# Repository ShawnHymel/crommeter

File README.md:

# Crommeter SAO

> SHOW ME WHAT YOU GOT

Badge accessory (SAO) to measure general sound level from cheers and applause. Gives a (somewhat) precise measurement of sound pressure level in dB.

This was made in Rust for no other reason than to test my embedded Rust skills.

## Build the Project

To build the project, you'll need Rust on your computer. Follow the [instructions here to install Rust](https://www.rust-lang.org/tools/install).

Next, install the Thumbv8m target processor:

```sh
rustup target add thumbv8m.main-none-eabihf
```

Navigate into the firmware directory and build the project:

```sh
cd firmware/crommeter/
cargo build --release
```

You can either flash the output ELF file (in *target/thumbv8m.main-none-eabihf/release*) using the [Raspberry Pi Debug Probe](https://www.raspberrypi.com/documentation/microcontrollers/debug-probe.html) or you can convert the ELF file to a UF2 file to flash over the USB mass storage device bootloader. To do the latter, you'll need to install [picotool](https://github.com/raspberrypi/picotool).

## (Optional) Install picotool

I recommend downloading one of the pre-compiled releases of picotool from [here](https://github.com/raspberrypi/pico-sdk-tools/releases). Unzip the file somewhere on your computer.

### Windows

Copy the *picotool/* folder to a place like *C:\Program Files\picotool\*.

Update PATH:

 1. Press **Win + R**, type `sysdm.cpl`, press **Enter**
 2. Go to the **Advanced** tab and click **Environment Variables**
 3. Under *User variables* or *System variables*, find *Path*
 4. Click **Edit > New** and add: `C:\Program Files\picotool`
 5. Click **OK** on all dialogs
 6. Restart your terminal/command prompt

### Linux

Copy picotool to your user local bin folder:

```sh
mkdir -p ~/.local/bin
cp picotool ~/.local/bin/
chmod +x ~/.local/bin/picotool
```

Update PATH: add the following to *~/.bashrc*:

```sh
export PATH="$HOME/.local/bin:$PATH"
```

Reload:

```sh
source ~/.bashrc
```

### macOS

Copy picotool to your user local bin folder:

```sh
mkdir -p ~/.local/bin
cp picotool ~/.local/bin/
chmod +x ~/.local/bin/picotool
```

Update PATH: add the following to *~/.zshrc*:

```sh
export PATH="$HOME/.local/bin:$PATH"
```

Reload:

```sh
source ~/.zshrc
```

## Run picotool and Flash

Once you have picotool installed, you can convert the ELF file to a UF2 file. Navigate to the firmware's directory and run:

```sh
cd firmware/crommeter/
picotool uf2 convert target/thumbv8m.main-none-eabihf/release/crommeter -t elf firmware.uf2
```

Hold the BOOT button on the RP2350 stamp and press/release the RESET button while the board is plugged into your computer. That should put the RP2350 into bootloader mode, which enumerates as a mass storage device on your computer. Then, simply copy the *firmware.uf2* file you just created to the RP2350 drive. The board should automatically reset and start running the firmware!

## License

The hardware files are released under [Creative Commons Attribution 4.0 International (CC BY 4.0)](https://creativecommons.org/licenses/by/4.0/).

Code in the firmware directory, unless otherwise noted, is licensed under the [Zero-Clause BSD license](https://opensource.org/license/0bsd) (0BSD).

```
Zero-Clause BSD
=============

Permission to use, copy, modify, and/or distribute this software for
any purpose with or without fee is hereby granted.

THE SOFTWARE IS PROVIDED “AS IS” AND THE AUTHOR DISCLAIMS ALL
WARRANTIES WITH REGARD TO THIS SOFTWARE INCLUDING ALL IMPLIED WARRANTIES
OF MERCHANTABILITY AND FITNESS. IN NO EVENT SHALL THE AUTHOR BE LIABLE
FOR ANY SPECIAL, DIRECT, INDIRECT, OR CONSEQUENTIAL DAMAGES OR ANY
DAMAGES WHATSOEVER RESULTING FROM LOSS OF USE, DATA OR PROFITS, WHETHER IN
AN ACTION OF CONTRACT, NEGLIGENCE OR OTHER TORTIOUS ACTION, ARISING OUT
OF OR IN CONNECTION WITH THE USE OR PERFORMANCE OF THIS SOFTWARE.
```

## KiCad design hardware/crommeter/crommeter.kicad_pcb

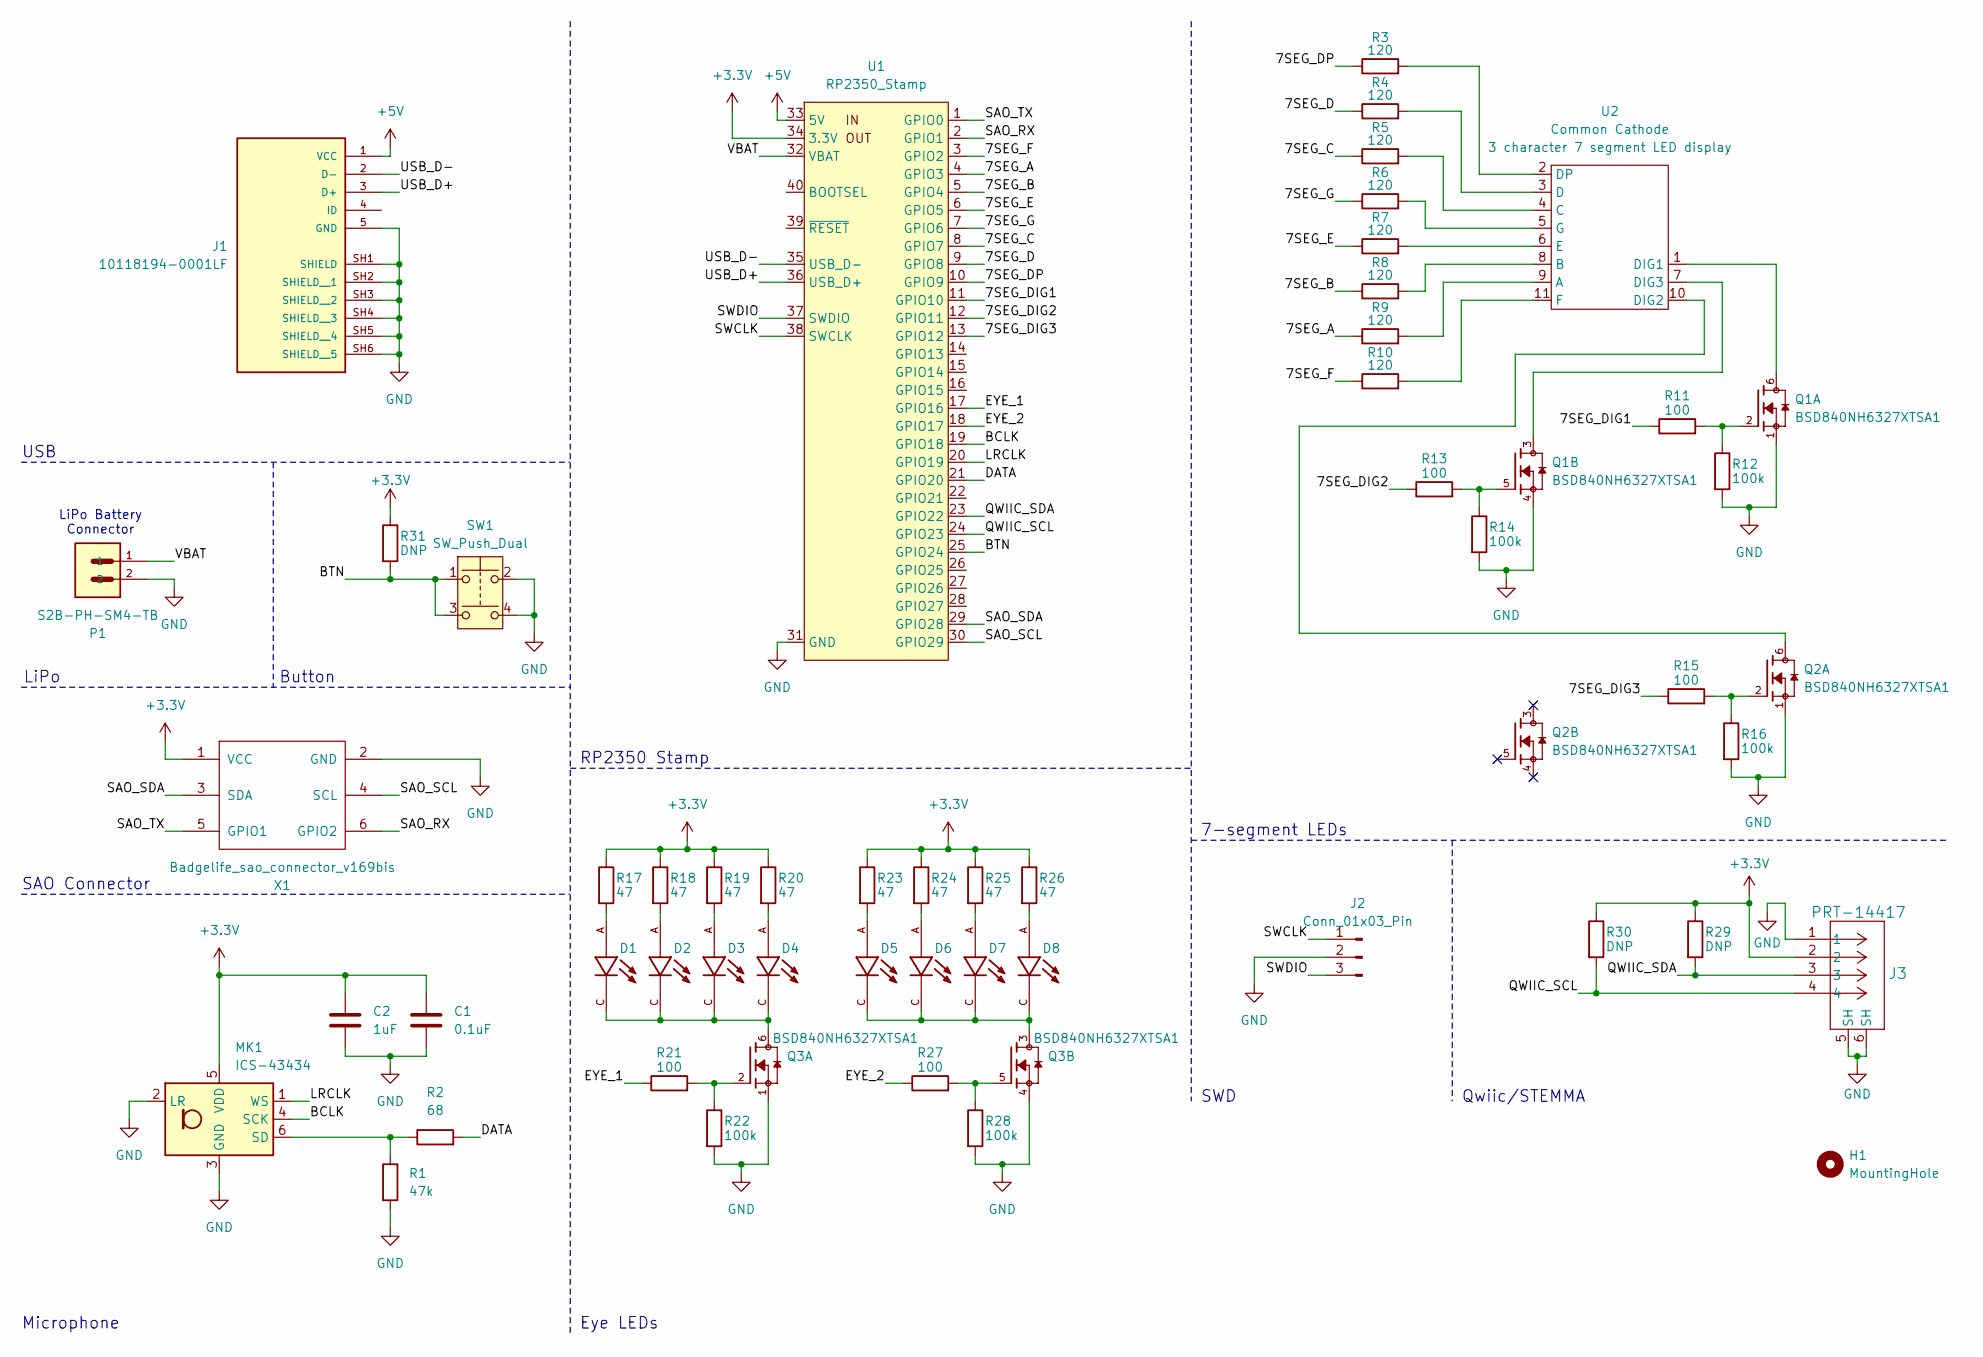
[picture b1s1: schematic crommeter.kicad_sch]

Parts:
C1: 0.1uF; C_0603_1608Metric_Pad1.08x0.95mm_HandSolder
C2: 1uF; C_0603_1608Metric_Pad1.08x0.95mm_HandSolder
D1, D2, D3, D4, D5, D6, D7, D8: CUW_Y3SH.B2-GFJD-5J6T-Z242-20-R18-Z; LED_CUW_Y3SH.B2-GFJD-5J6T-Z242-20-R18-Z; PARTREV 1.0
H1: MountingHole; MountingHole_4.3mm_M4
J1: 10118194-0001LF; AMPHENOL_10118194-0001LF; PARTREV D
J2: Conn_01x03_Pin; AMPHENOL_10129380-903001BLF
J3: PRT-14417; CONN_PRT-14417_SPK
MK1: ICS-43434; InvenSense_ICS-43434-6_3.5x2.65mm
P1: S2B-PH-SM4-TB; JST_S2B-PH-SM4-TB
Q1, Q2, Q3: BSD840NH6327XTSA1; TRANS_BSD840NH6327XTSA1; PARTREV 2.4
R1: 47k; R_0603_1608Metric_Pad0.98x0.95mm_HandSolder
R2: 68; R_0603_1608Metric_Pad0.98x0.95mm_HandSolder
R3, R4, R5, R6, R7, R8, R9, R10: 120; R_0603_1608Metric_Pad0.98x0.95mm_HandSolder
R11, R13, R15, R21, R27: 100; R_0603_1608Metric_Pad0.98x0.95mm_HandSolder
R12, R14, R16, R22, R28: 100k; R_0603_1608Metric_Pad0.98x0.95mm_HandSolder
R17, R18, R19, R20, R23, R24, R25, R26: 47; R_0603_1608Metric_Pad0.98x0.95mm_HandSolder
R29, R30, R31: DNP; R_0603_1608Metric_Pad0.98x0.95mm_HandSolder
SW1: SW_Push_Dual; SWITCH_FSM2JSMAA_TYC
U1: RP2350_Stamp; RP2xxx_Stamp_SMD
U2: Common Cathode; SDTx40R2W
X1: Badgelife_sao_connector_v169bis; Badgelife-SAOv169-SAO-2x3

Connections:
+3.3V: C1.1, C2.1, J3.2, MK1.5 (VDD), R17.1, R18.1, R19.1, R20.1, R23.1, R24.1, R25.1, R26.1, R29.1, R30.1, R31.1, U1.34 (3.3V), X1.1 (VCC)
+5V: J1.1 (VCC), U1.33 (5V)
/7SEG_A: R9.1, U1.4 (GPIO3)
/7SEG_B: R8.1, U1.5 (GPIO4)
/7SEG_C: R5.1, U1.8 (GPIO7)
/7SEG_D: R4.1, U1.9 (GPIO8)
/7SEG_DIG1: R11.1, U1.11 (GPIO10)
/7SEG_DIG2: R13.1, U1.12 (GPIO11)
/7SEG_DIG3: R15.1, U1.13 (GPIO12)
/7SEG_DP: R3.1, U1.10 (GPIO9)
/7SEG_E: R7.1, U1.6 (GPIO5)
/7SEG_F: R10.1, U1.3 (GPIO2)
/7SEG_G: R6.1, U1.7 (GPIO6)
/<NO NET>: U1.29 (GPIO28), X1.3 (SDA)
/BCLK: MK1.4 (SCK), U1.19 (GPIO18)
/BTN: R31.2, SW1.1, SW1.3, U1.25 (GPIO24)
/DATA: R2.2, U1.21 (GPIO20)
/EYE_1: R21.1, U1.17 (GPIO16)
/EYE_2: R27.1, U1.18 (GPIO17)
/LRCLK: MK1.1 (WS), U1.20 (GPIO19)
/QWIIC_SCL: J3.4, R30.2, U1.24 (GPIO23)
/QWIIC_SDA: J3.3, R29.2, U1.23 (GPIO22)
/SAO_RX: U1.2 (GPIO1), X1.6 (GPIO2)
/SAO_SCL: U1.30 (GPIO29), X1.4 (SCL)
/SAO_TX: U1.1 (GPIO0), X1.5 (GPIO1)
/SWCLK: J2.1, U1.38 (SWCLK)
/SWDIO: J2.3, U1.37 (SWDIO)
/USB_D+: J1.3 (D+), U1.36 (USB_D+)
/USB_D-: J1.2 (D-), U1.35 (USB_D-)
/VBAT: P1.1, U1.32 (VBAT)
GND: C1.2, C2.2, J1.5 (GND), J1.SH1 (SHIELD), J1.SH2 (SHIELD__1), J1.SH3 (SHIELD__2), J1.SH4 (SHIELD__3), J1.SH5 (SHIELD__4), J1.SH6 (SHIELD__5), J2.2, J3.1, J3.5 (SH), J3.6 (SH), MK1.2 (LR), MK1.3 (GND), P1.2, Q1.1, Q1.4, Q2.1, Q3.1, Q3.4, R1.2, R12.2, R14.2, R16.2, R22.2, R28.2, SW1.2, SW1.4, U1.31 (GND), X1.2 (GND)
unnamed: D1.A, R17.2
unnamed: D1.C, D2.C, D3.C, D4.C, Q3.6
unnamed: D2.A, R18.2
unnamed: D3.A, R19.2
unnamed: D4.A, R20.2
unnamed: D5.A, R23.2
unnamed: D5.C, D6.C, D7.C, D8.C, Q3.3
unnamed: D6.A, R24.2
unnamed: D7.A, R25.2
unnamed: D8.A, R26.2
unnamed: MK1.6 (SD), R1.1, R2.1
unnamed: Q1.2, R11.2, R12.1
unnamed: Q1.5, R13.2, R14.1
unnamed: Q2.2, R15.2, R16.1
unnamed: Q3.2, R21.2, R22.1
unnamed: Q3.5, R27.2, R28.1
unnamed: R9.2, U2.9 (A)
unnamed: R8.2, U2.8 (B)
unnamed: R5.2, U2.4 (C)
unnamed: R4.2, U2.3 (D)
unnamed: Q1.6, U2.1 (DIG1)
unnamed: Q2.6, U2.10 (DIG2)
unnamed: Q1.3, U2.7 (DIG3)
unnamed: R3.2, U2.2 (DP)
unnamed: R7.2, U2.6 (E)
unnamed: R10.2, U2.11 (F)
unnamed: R6.2, U2.5 (G)

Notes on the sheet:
7-segment LEDs
RP2350 Stamp
Microphone
USB
LiPo Battery Connector
Eye LEDs
Button
Qwiic/STEMMA
LiPo
SAO Connector
SWD

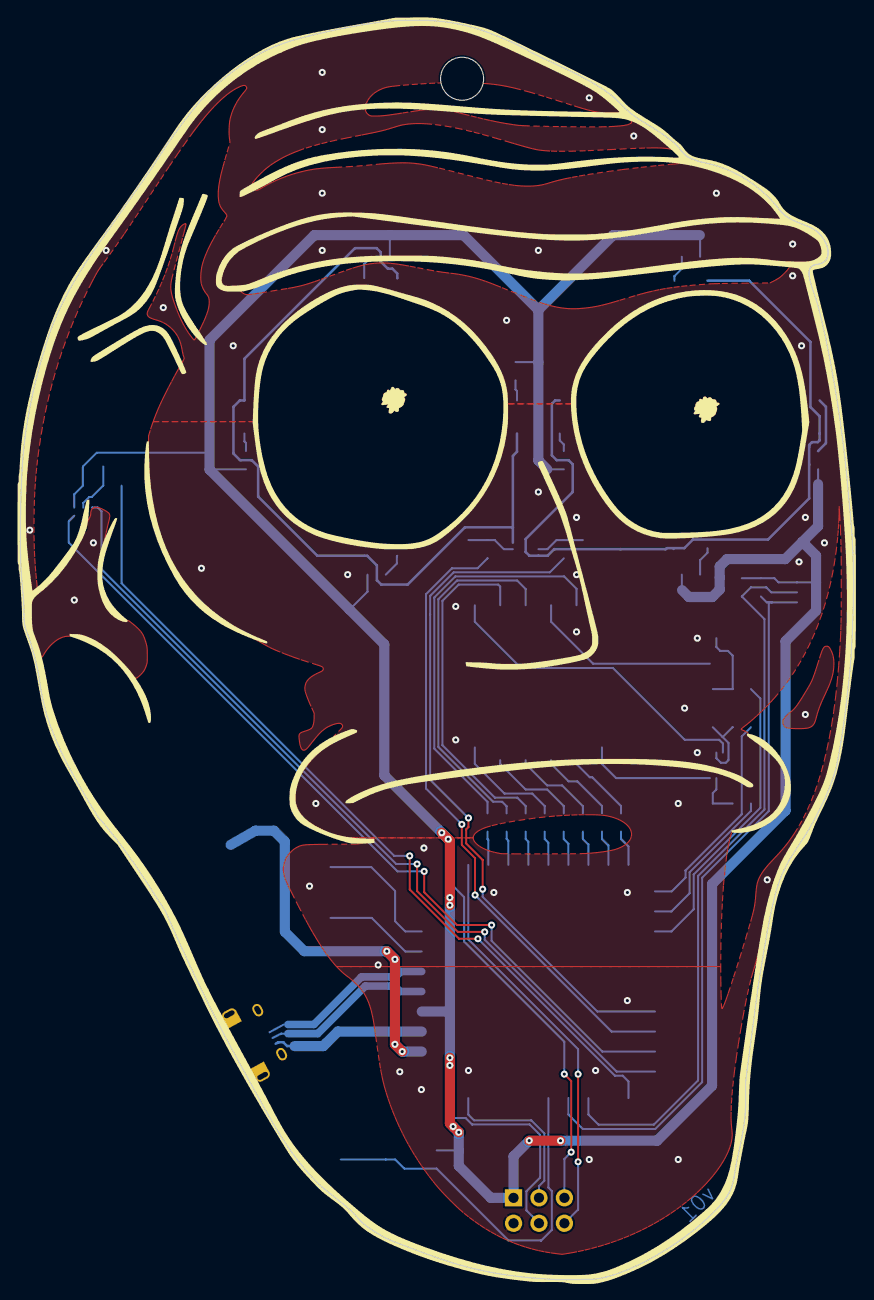
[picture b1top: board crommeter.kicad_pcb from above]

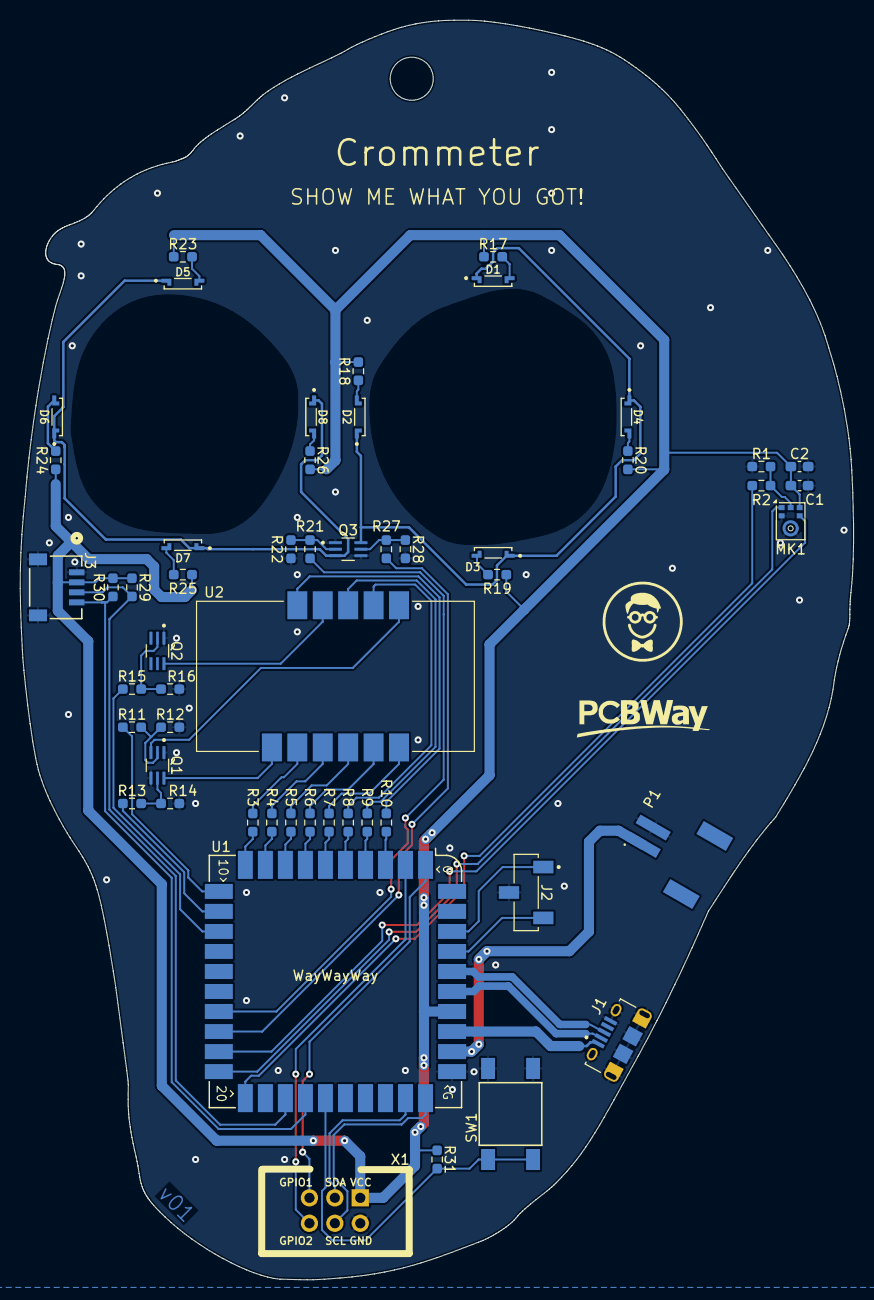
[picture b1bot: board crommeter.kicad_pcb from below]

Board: 4 copper layers, 83.2 x 125.8 mm, 54 parts (52 on the bottom side), 58 nets.

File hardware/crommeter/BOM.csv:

"Reference","Qty","Value","Footprint","MANUFACTURER","Manufacturer Part Number","Part Link","Footprint Link"
"C1","1","0.1uF","Capacitor_SMD:C_0603_1608Metric_Pad1.08x0.95mm_HandSolder","YAGEO","CC0603KRX7R7BB104","https://www.digikey.com/en/products/detail/yageo/CC0603KRX7R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",""
"C2","1","1uF","Capacitor_SMD:C_0603_1608Metric_Pad1.08x0.95mm_HandSolder","YAGEO","CC0603KRX7R7BB105","https://www.digikey.com/en/products/detail/yageo/CC0603KRX7R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",""
"D1,D2,D3,D4,D5,D6,D7,D8","8","CUW_Y3SH.B2-GFJD-5J6T-Z242-20-R18-Z","CUW_Y3SH_B2_GFJD_5J6T_Z242_20_R18_Z:LED_CUW_Y3SH.B2-GFJD-5J6T-Z242-20-R18-Z","OSRAM Opto Semiconductors Inc.","CUW Y3SH.B2-GFJD-5J6T-Z242-20-R18-Z","https://www.digikey.com/en/products/detail/ams-osram-usa-inc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","https://www.digikey.com/en/models/13998110"
"H1","1","MountingHole","MountingHole:MountingHole_4.3mm_M4","","","",""
"J1","1","10118194-0001LF","10118194_0001LF:AMPHENOL_10118194-0001LF","Amphenol","10118194-0001LF","https://www.digikey.com/en/products/detail/amphenol-cs-fci/1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","https://www.digikey.com/en/models/2785389"
"J2","1","Conn_01x03_Pin","10129380-903001BLF:AMPHENOL_10129380-903001BLF","Amphenol ICC (FCI)","10129380-903001BLF","https://www.digikey.com/en/products/detail/amphenol-cs-fci/1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","https://www.digikey.com/en/models/7916034"
"J3","1","PRT-14417","qwiic_connector:CONN_PRT-14417_SPK","SparkFun Electronics","14417","https://www.digikey.com/en/products/detail/sparkfun-electron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","https://www.digikey.com/en/models/7652746"
"MK1","1","ICS-43434","Sensor_Audio:InvenSense_ICS-43434-6_3.5x2.65mm","TDK InvenSense","ICS-43434","https://www.digikey.com/en/products/detail/tdk-invensense/IC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","https://www.digikey.com/en/models/6140298"
"P1","1","S2B-PH-SM4-TB","S2B-PH-SM4-TB:JST_S2B-PH-SM4-TB","JST","S2B-PH-SM4-TB","https://www.digikey.com/en/products/detail/jst-sales-america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","https://www.digikey.com/en/models/926655"
"Q1,Q2,Q3","3","BSD840NH6327XTSA1","BSD840NH6327XTSA1:TRANS_BSD840NH6327XTSA1","INFINEON","BSD840NH6327XTSA1","https://www.digikey.com/en/products/detail/infineon-technolo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","https://www.digikey.com/en/models/2783455"
"R1","1","47k","Resistor_SMD:R_0603_1608Metric_Pad0.98x0.95mm_HandSolder","YAGEO","RC0603FR-0747KL","https://www.digikey.com/en/products/detail/yageo/RC0603FR-07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",""
"R2","1","68","Resistor_SMD:R_0603_1608Metric_Pad0.98x0.95mm_HandSolder","YAGEO","RC0603FR-0768RL","https://www.digikey.com/en/products/detail/yageo/RC0603FR-07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",""
"R3,R4,R5,R6,R7,R8,R9,R10","8","120","Resistor_SMD:R_0603_1608Metric_Pad0.98x0.95mm_HandSolder","YAGEO","RC0603JR-7W120RL","https://www.digikey.com/en/products/detail/yageo/RC0603JR-7W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",""
"R11,R13,R15,R21,R27","5","100","Resistor_SMD:R_0603_1608Metric_Pad0.98x0.95mm_HandSolder","YAGEO","RC0603FR-7W100RL","https://www.digikey.com/en/products/detail/yageo/RC0603FR-7W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",""
"R12,R14,R16,R22,R28","5","100k","Resistor_SMD:R_0603_1608Metric_Pad0.98x0.95mm_HandSolder","YAGEO","RC0603FR-07100KL","https://www.digikey.com/en/products/detail/yageo/RC0603FR-07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",""
"R17,R18,R19,R20,R23,R24,R25,R26","8","47","Resistor_SMD:R_0603_1608Metric_Pad0.98x0.95mm_HandSolder","YAGEO","RC0603FR-1347RL","https://www.digikey.com/en/products/detail/yageo/RC0603FR-13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",""
"R29,R30,R31","3","DNP","Resistor_SMD:R_0603_1608Metric_Pad0.98x0.95mm_HandSolder","","","",""
"SW1","1","SW_Push_Dual","FSM2JSMAATR:SWITCH_FSM2JSMAA_TYC","TE Connectivity ALCOSWITCH Switches","FSM2JSMAATR","https://www.digikey.com/en/products/detail/te-connectivity-a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","https://www.digikey.com/en/models/1201469"
"U1","1","RP2350_Stamp","RP2xxx_Stamp:RP2xxx_Stamp_SMD","Solder Party","RP2350 Stamp","https://shop.pimoroni.com/products/rp2350-stamp","https://github.com/solderparty/rp2xxx_stamp_footprints"
"U2","1","Common Cathode","custom:SDTx40R2W","ChromeLED","SDTC40R2W","https://www.digikey.com/en/products/detail/chromeled/SDTC40R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",""
"X1","1","Badgelife_sao_connector_v169bis","badgelife_sao_v169bis:Badgelife-SAOv169-SAO-2x3","Adam Tech","BHR-06-VUA","https://www.digikey.com/en/products/detail/adam-tech/BHR-06-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","https://cdn.hackaday.io/files/1751827494986688/KiCad_SAOv2.zip"

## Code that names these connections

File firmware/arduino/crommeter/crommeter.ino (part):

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
// LED and button
#define LED_PIN       29
#define BTN_PIN       24

// I2S pins
#define I2S_DATA_PIN  20
#define I2S_BCLK_PIN  18  // Note that LRCLK is set to BCLK + 1

// 7-segment display pins
#define SEG_A         3
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  pinMode(EYE_R_PIN, OUTPUT);

  // Setup button with pullup and interrupt
  pinMode(BTN_PIN, INPUT_PULLUP);

  // Initialize serial and wait for connection
  DEBUG_BEGIN(115200);
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}

void loop() {
  bool buttonReading = digitalRead(BTN_PIN);
  
  // Check if button state changed
  if (buttonReading != lastButtonReading) {
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
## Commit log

2025-09-18 Initial commit with working blinky
2025-09-19 Added initial microphone test
2025-09-19 Ping pong buffer kinda works. Logging causes overflow.
2025-09-20 Got some help from Claude. Some progress in getting the ping-pong buffer working.
2025-09-22 Initial KiCad schematic done
2025-09-23 Finished schematic. Parts placed in general areas.
2025-09-24 Added artwork
2025-09-26 Mostly finished layout
2025-09-27 Generated gerbers
2025-09-30 Created gerbers
2025-10-15 Added BOM
2025-10-16 Hardcoded 32 bit depth for PIO I2S program
2025-11-01 Working at Supercon

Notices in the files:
hardware/crommeter/crommeter.kicad_sch:
License: CC BY 4.0
